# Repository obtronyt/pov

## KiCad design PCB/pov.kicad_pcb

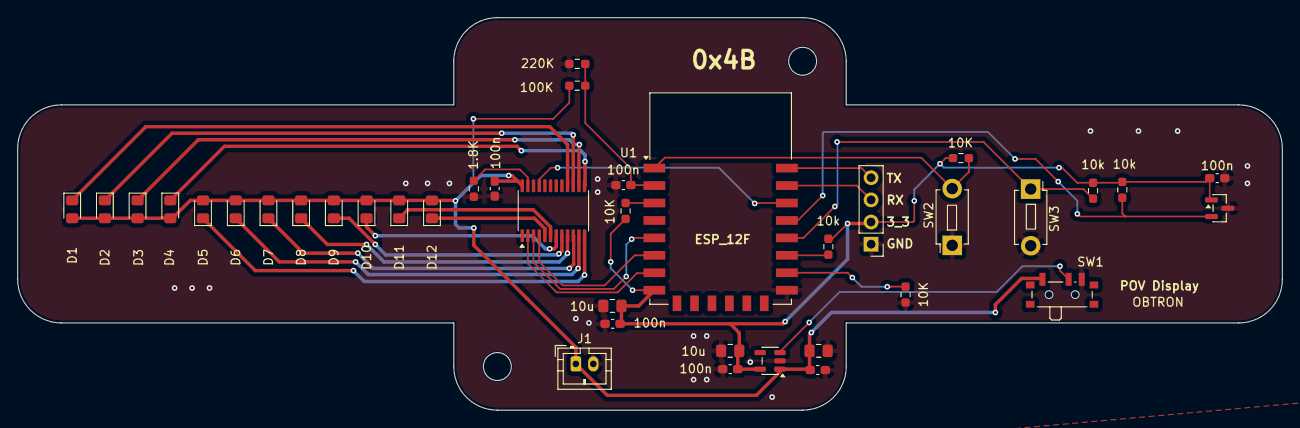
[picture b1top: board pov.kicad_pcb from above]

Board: 2 copper layers, 145.0 x 45.0 mm, 39 parts (0 on the bottom side), 30 nets.

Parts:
1.8K: 1.8K; R_0603_1608Metric_Pad0.98x0.95mm_HandSolder
10K: 10k; R_0603_1608Metric_Pad0.98x0.95mm_HandSolder
100n: 100n; C_0603_1608Metric_Pad1.08x0.95mm_HandSolder
C1, C3, C5, C7, C9: 100n; C_0603_1608Metric_Pad1.08x0.95mm_HandSolder
C2, C4, C6: 10u; C_0805_2012Metric_Pad1.18x1.45mm_HandSolder
D1, D2, D3, D4, D5, D6, D7, D8, D9, D10, D11, D12: LED; LED_0805_2012Metric_Pad1.15x1.40mm_HandSolder
GND: Program Header; PinHeader_1x04_P2.54mm_Vertical
J1: Conn_01x02_Pin; JST_PH_B2B-PH-K_1x02_P2.00mm_Vertical
R1: 100K; R_0603_1608Metric_Pad0.98x0.95mm_HandSolder
R2: 220K; R_0603_1608Metric_Pad0.98x0.95mm_HandSolder
R3, R4: 10K; R_0603_1608Metric_Pad0.98x0.95mm_HandSolder
R6, R7, R9: 10k; R_0603_1608Metric_Pad0.98x0.95mm_HandSolder
SW1: SW_SPDT; SW_SPDT_PCM12
SW2, SW3: SW_Push; SW_PUSH_1P1T_6x3.5mm_H4.3_APEM_MJTP1243
U1: ESP-12F; ESP-12E
U3: AP2112K-3.3; SOT-23-5
U4: TLC5926; TSSOP-24_4.4x7.8mm_P0.65mm
U5: H.F.S; SOT-23

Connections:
3_3_LDO: C4.1, C5.1, C6.2, C7.2, C9.2, GND.2, R3.1, R4.1, R6.1, R7.1, R9.2, U1.8 (VCC), U3.5 (VOUT), U5.1 (VCC)
GND: 1.8K.2, 10K.2, 100n.1, C1.2, C2.2, C3.2, C4.2, C5.2, C6.1, C7.1, C9.1, GND.1, J1.2, R2.2, SW1.3 (C), SW2.1, SW3.2, U1.15 (GND), U3.2 (GND), U4.1 (GND), U5.3 (GND)
unnamed: D1.1 (K), U4.16 (OUT11)
unnamed: D2.1 (K), U4.15 (OUT10)
unnamed: D3.1 (K), U4.14 (OUT9)
unnamed: D4.1 (K), U4.13 (OUT8)
unnamed: D5.1 (K), U4.12 (OUT7)
unnamed: D6.1 (K), U4.11 (OUT6)
unnamed: D7.1 (K), U4.10 (OUT5)
unnamed: D8.1 (K), U4.9 (OUT4)
unnamed: D9.1 (K), U4.8 (OUT3)
unnamed: D10.1 (K), U4.7 (OUT2)
unnamed: D11.1 (K), U4.6 (OUT1)
unnamed: D12.1 (K), U4.5 (OUT0)
unnamed: GND.3, U1.21 (GPIO3/RXD)
unnamed: GND.4, U1.22 (GPIO1/TXD)
unnamed: SW1.2 (B), U3.3 (EN)
unnamed: C1.1, R1.2, R2.1, U1.2 (ADC)
unnamed: R4.2, U1.3 (EN)
unnamed: R6.2, SW3.1, U1.18 (GPIO0)
unnamed: R7.2, U1.17 (GPIO2)
unnamed: R9.1, U1.19 (GPIO4), U5.2 (OUT)
unnamed: U1.20 (GPIO5), U4.21 (PWCLK)
unnamed: U1.6 (GPIO12), U4.4 (LE)
unnamed: U1.7 (GPIO13), U4.2 (SDI)
unnamed: U1.5 (GPIO14), U4.3 (CLK)
unnamed: 10K.1, U1.16 (GPIO15)
unnamed: R3.2, SW2.2, U1.1 (~RST)
unnamed: 1.8K.1, U4.23 (R-EXT)
Vbatt: 100n.2, C2.1, C3.1, D1.2 (A), D2.2 (A), D3.2 (A), D4.2 (A), D5.2 (A), D6.2 (A), D7.2 (A), D8.2 (A), D9.2 (A), D10.2 (A), D11.2 (A), D12.2 (A), J1.1, R1.1, SW1.1 (A), U3.1 (VIN), U4.24 (VDD)

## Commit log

2026-01-31 Init
2026-01-31 Pcb files
2026-01-31 3dprint files
2026-02-01 Sliding text api
2026-02-01 basic seuqnece
2026-02-01 Img to bitmaps
2026-02-01 Smiley animation (buggy)
2026-02-05 Battery level+dynamic slice
2026-02-06 Add kicker and dancer animation
2026-04-05 Added randomSparkle and eye animations
2026-04-09 sine wave
2026-04-09 sine wave reset fix
